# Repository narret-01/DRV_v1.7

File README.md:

High speed HB driver, up to 20A output. 
It's 2 Layer board, based on NSI6602A.
Board size is 59 x 38.5mm.
Maded in EagleCad.

Top side assembled

Top 3d

Top

Bot

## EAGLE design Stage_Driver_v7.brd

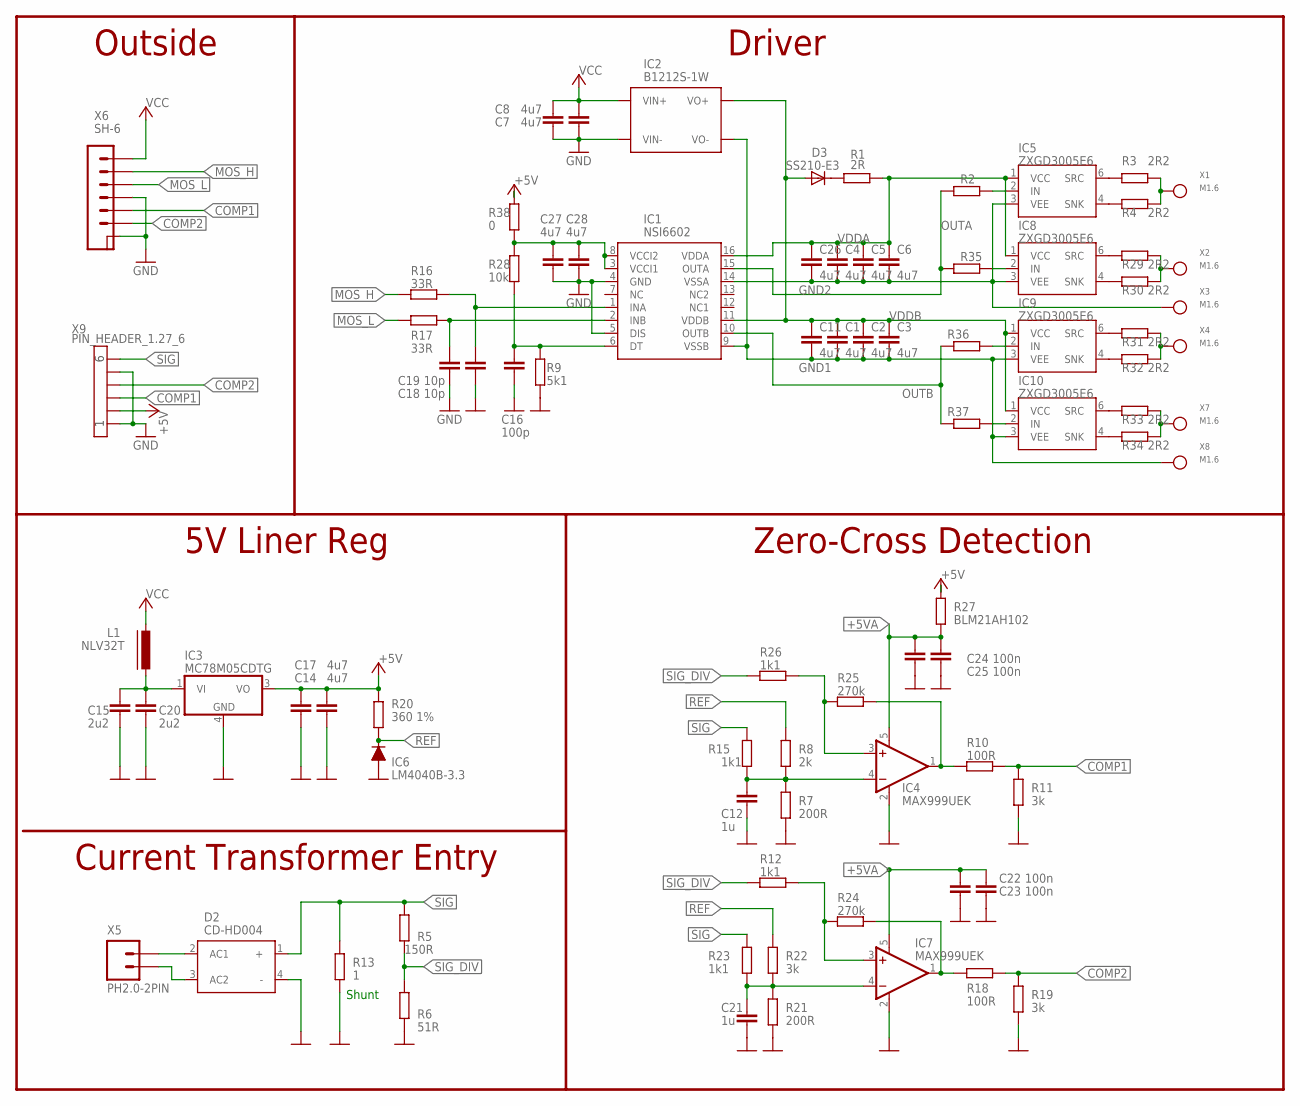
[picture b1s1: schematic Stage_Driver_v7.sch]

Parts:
C1, C2, C3, C4, C5, C6, C7, C8, C11, C14, C17, C26: 4u7; C0805
C12, C21: 1u; C0603
C15, C20: 2u2; C0805
C16: 100p; C0603
C18, C19: 10p; C0603
C22, C23, C24, C25: 100n; C0603
C27, C28: 4u7; C0603
D2: CD-HD004; CD-HD0X
D3: SS210-E3; DO-214AA(SMB)
IC1: NSI6602; SOIC16
IC2: B1212S-1W; BS-1WR3
IC3: MC78M05CDTG; DPACK_3
IC4, IC7: MAX999UEK; SOT-23-5
IC5, IC8, IC9, IC10: ZXGD3005E6; SOT-23-6
IC6: LM4040B-3.3; SOT-23
L1: NLV32T
R1: 2R; R1210
R2, R35, R36, R37: R-EU_R0603; R0603
R3, R4, R29, R30, R31, R32, R33, R34: 2R2; R0603
R5: 150R; R0805
R6: 51R; R0805
R7, R21: 200R; R0603
R8: 2k; R0603
R9: 5k1; R0603
R10, R18: 100R; R0603
R11, R19, R22: 3k; R0603
R12, R15, R23, R26: 1k1; R0603
R13: 1; R1210
R16, R17: 33R; R0603
R20: 360 1%; R0805
R24, R25: 270k; R0603
R27: BLM21AH102; R0805
R28: 10k; R0603
R38: 0; R0805
X1, X2, X3, X4, X7, X8: M1.6
X5: PH2.0-2PIN
X6: SH-6
X9: PIN_HEADER_1.27_6

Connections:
+5V: C14.1, C17.1, IC3.3 (VO), R20.2, R27.1, R38.2, X9.P$2
+5VA: C22.1, C23.1, C24.1, C25.1, IC4.5 (V+), IC7.5 (V+), R27.2
COMP1: R10.1, R11.1, X6.P$5 (5), X9.P$3
COMP2: R18.1, R19.1, X6.P$6 (6), X9.P$4
GND: C7.2, C8.2, C12.2, C14.2, C15.2, C16.2, C17.2, C18.2, C19.2, C20.2, C21.2, C22.2, C23.2, C24.2, C25.2, C27.2, C28.2, D2.4 (-), IC1.4 (GND), IC1.5 (DIS), IC2.P$1 (VIN-), IC3.4 (GND), IC4.2 (V-), IC6.2 (A), IC7.2 (V-), R6.1, R7.1, R9.1, R11.2, R13.1, R19.2, R21.1, X6.G1 (G), X6.G2 (G), X6.P$4 (4), X9.P$1, X9.P$5
GND1: C1.2, C2.2, C3.2, C11.2, IC1.9 (VSSB), IC2.P$3 (VO-), IC9.3 (VEE), IC10.3 (VEE), X8.P$1
GND2: C4.2, C5.2, C6.2, C26.2, IC1.14 (VSSA), IC5.3 (VEE), IC8.3 (VEE), X3.P$1
MOS_H: R16.2, X6.P$2 (2)
MOS_L: R17.2, X6.P$3 (3)
unnamed: IC7.3 (+IN), R12.2, R24.2
unnamed: D3.1 (C), R1.1
unnamed: C21.1, IC7.4 (-IN), R21.2, R22.1, R23.2
unnamed: D2.2 (AC1), X5.P$2 (2)
unnamed: IC5.6 (SRC), R3.1
unnamed: IC5.2 (IN), R2.2
unnamed: C27.1, C28.1, IC1.3 (VCCI1), IC1.8 (VCCI2), R28.2, R38.1
unnamed: IC7.1 (OUT), R18.2, R24.1
unnamed: C12.1, IC4.4 (-IN), R7.2, R8.1, R15.2
unnamed: C18.1, IC1.1 (INA), R16.1
unnamed: C19.1, IC1.2 (INB), R17.1
unnamed: C16.1, IC1.6 (DT), R9.2, R28.1
unnamed: IC4.1 (OUT), R10.2, R25.1
unnamed: D2.3 (AC2), X5.P$1 (1)
unnamed: C15.1, C20.1, IC3.1 (VI), L1.P$1 (1)
unnamed: IC4.3 (+IN), R25.2, R26.2
unnamed: IC5.4 (SNK), R4.1
unnamed: IC8.6 (SRC), R29.1
unnamed: IC8.4 (SNK), R30.1
unnamed: IC9.6 (SRC), R31.1
unnamed: IC9.4 (SNK), R32.1
unnamed: IC10.6 (SRC), R33.1
unnamed: IC10.4 (SNK), R34.1
unnamed: R29.2, R30.2, X2.P$1
unnamed: R31.2, R32.2, X4.P$1
unnamed: R33.2, R34.2, X7.P$1
unnamed: IC8.2 (IN), R35.2
unnamed: IC9.2 (IN), R36.2
unnamed: IC10.2 (IN), R37.2
OUTA: IC1.15 (OUTA), R2.1, R35.1
OUTB: IC1.10 (OUTB), R36.1, R37.1
REF: IC6.1 (K), R8.2, R20.1, R22.2
SIG: D2.1 (+), R5.1, R13.2, R15.1, R23.1, X9.P$6
SIG_DIV: R5.2, R6.2, R12.1, R26.1
VCC: C7.1, C8.1, IC2.P$2 (VIN+), L1.P$2 (2), X6.P$1 (1)
VDDA: C4.1, C5.1, C6.1, C26.1, IC1.16 (VDDA), IC5.1 (VCC), IC8.1 (VCC), R1.2
VDDB: C1.1, C2.1, C3.1, C11.1, D3.2 (A), IC1.11 (VDDB), IC2.P$4 (VO+), IC9.1 (VCC), IC10.1 (VCC)
X1-G: R3.2, R4.2, X1.P$1

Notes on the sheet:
Shunt
Current Transformer Entry
5V Liner Reg
Driver
Zero-Cross Detection
Outside

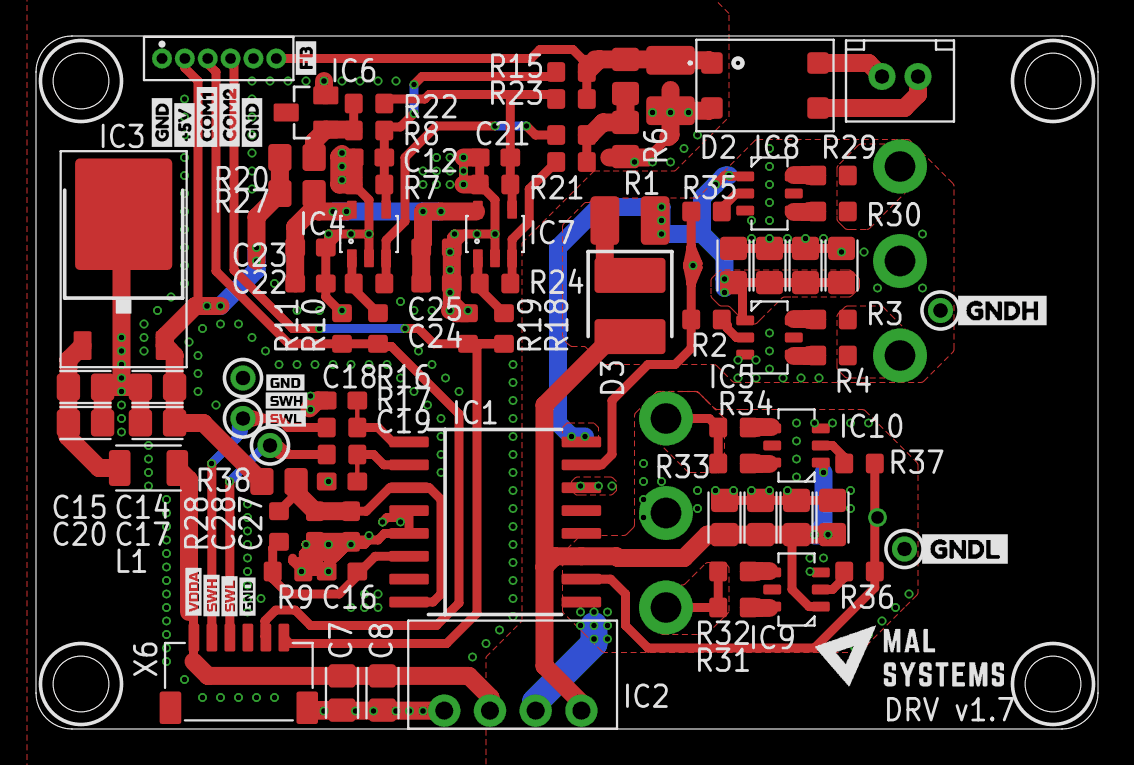
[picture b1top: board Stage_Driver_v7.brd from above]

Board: 2 copper layers, 59.0 x 38.5 mm, 100 parts (0 on the bottom side), 47 nets.

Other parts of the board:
U$1: #5V1
U$2: COM12
U$3, U$5, U$9, U$10: GND0
U$4: COM23
U$6: FB4
U$7, U$11: SWL7
U$8, U$12: SWH6
U$13: VDDA12
U$14: GNDL0
U$15: GNDH1
U$16: 14_#_#####_#_COPY#PNG

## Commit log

2024-01-09 1.First commit
2024-01-09 1.add radme
2024-01-09 1.readme edited
